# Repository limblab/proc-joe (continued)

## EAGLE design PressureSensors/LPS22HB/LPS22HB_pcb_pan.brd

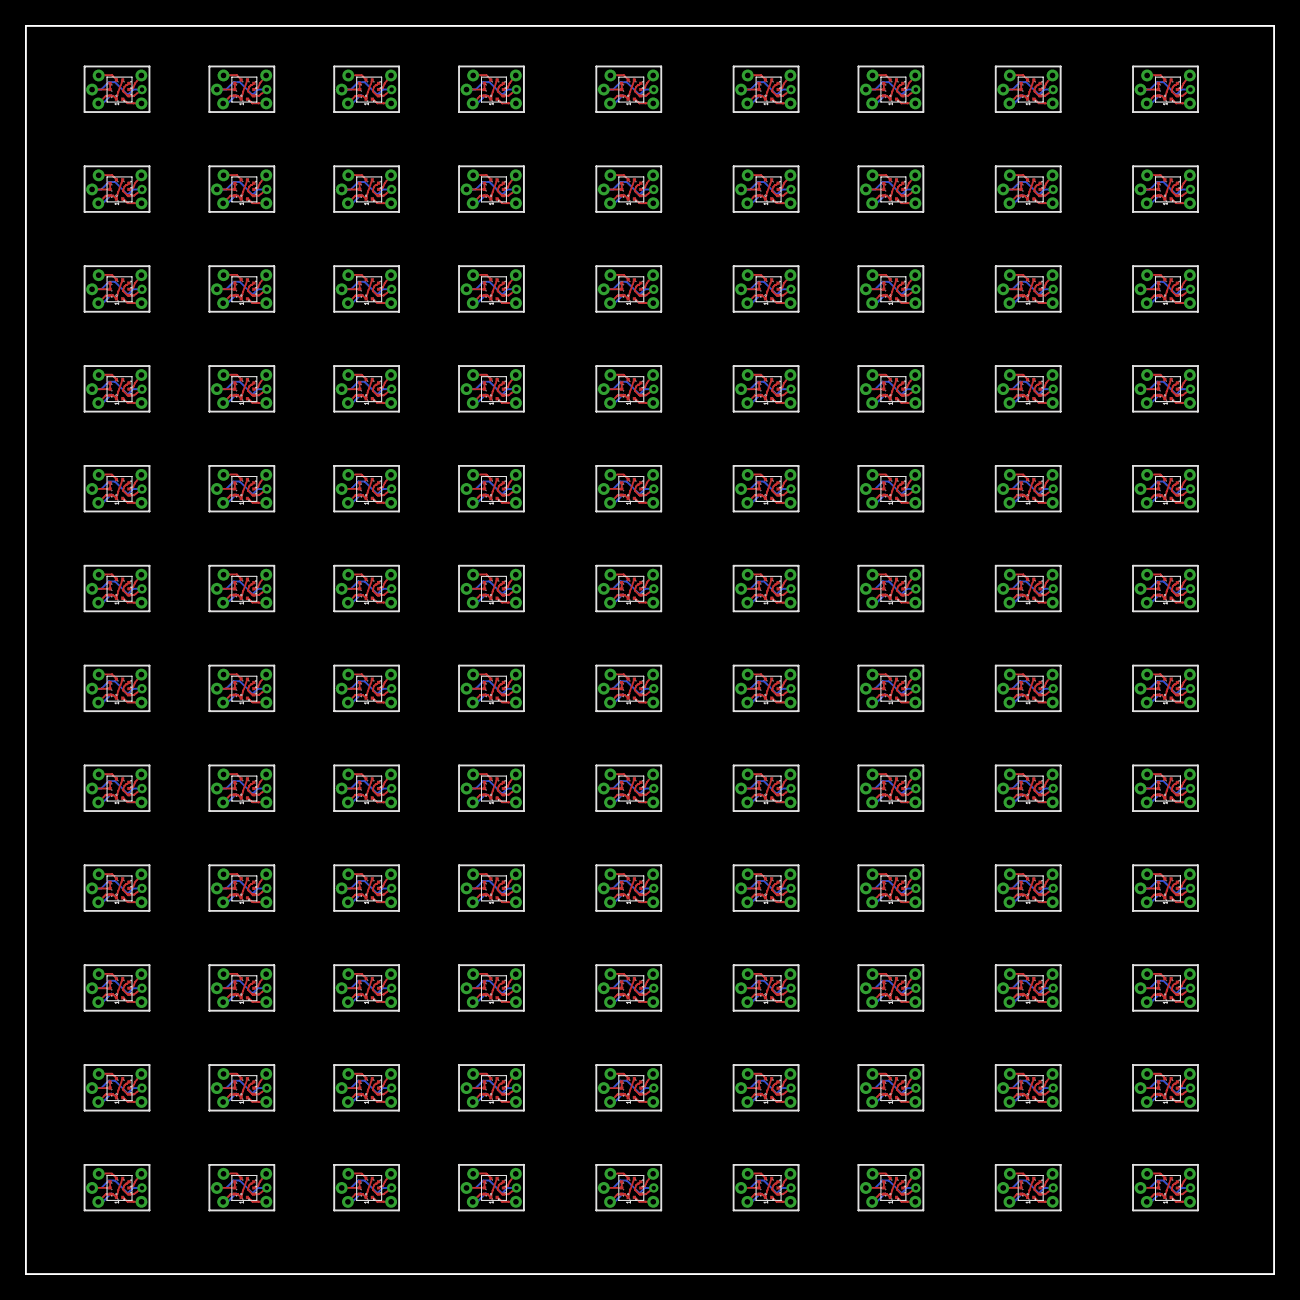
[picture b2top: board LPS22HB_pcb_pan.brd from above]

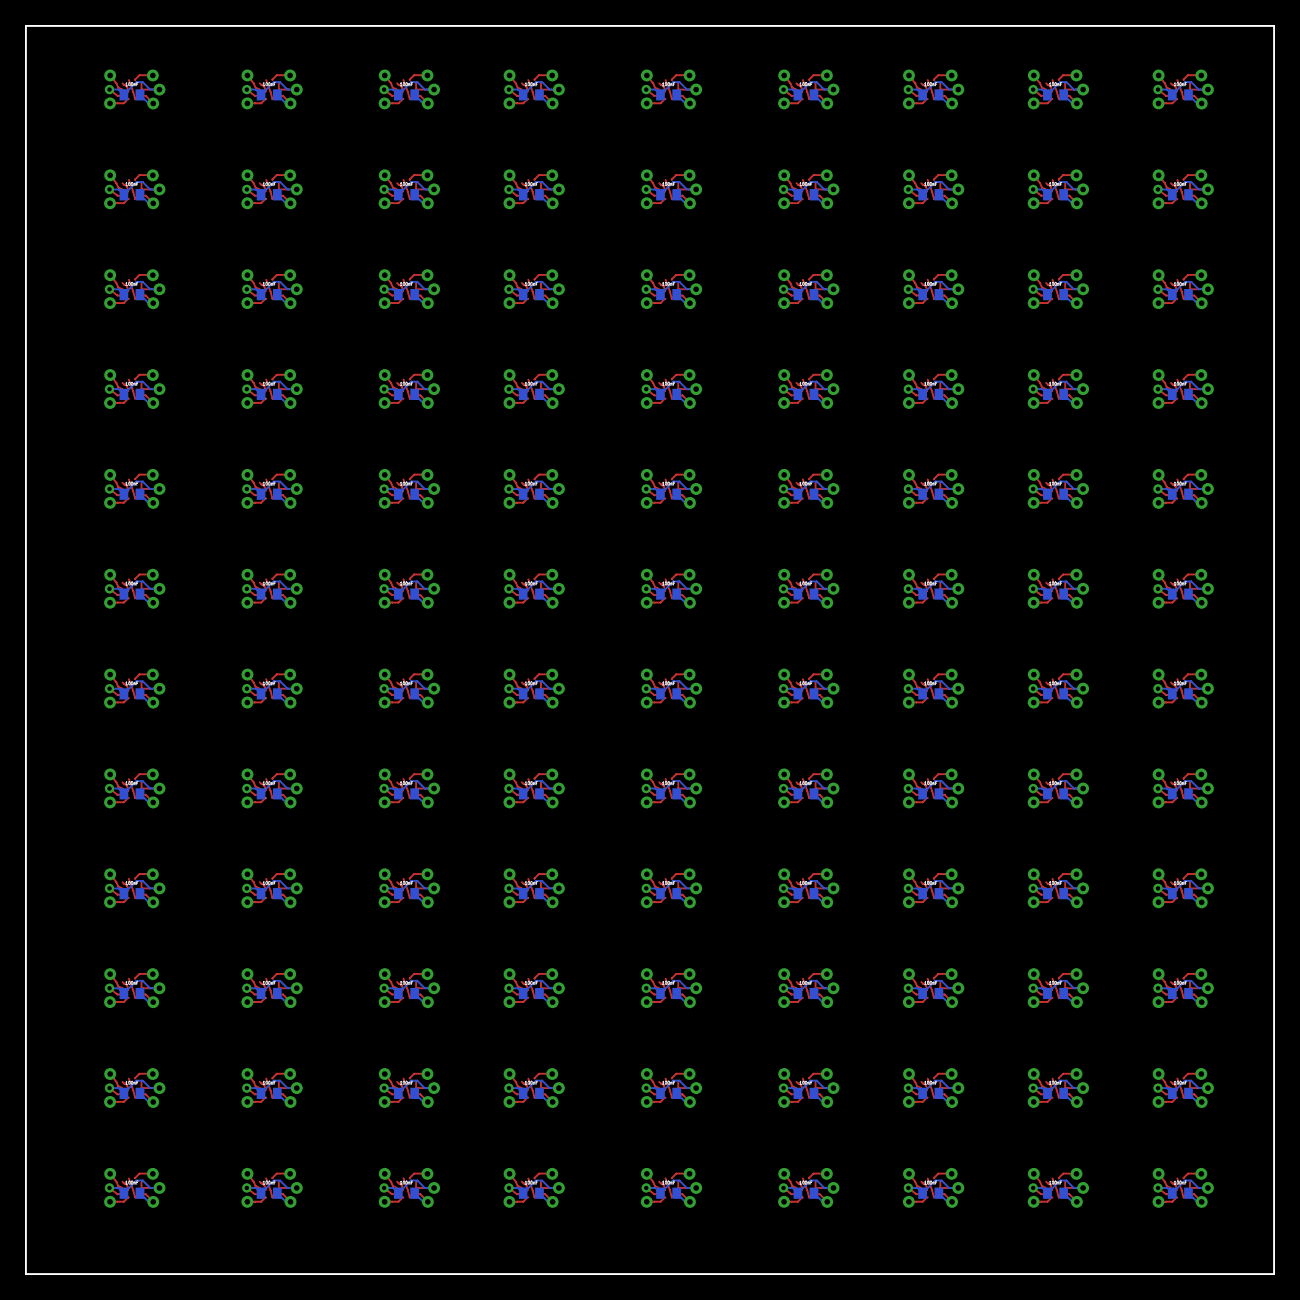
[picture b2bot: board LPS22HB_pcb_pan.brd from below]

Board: 2 copper layers, 100.0 x 100.0 mm, 756 parts (108 on the bottom side), 540 nets.

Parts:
C1, C2, C3, C4, C5, C6, C7, C8, C9, C10, C11, C12, C13, C14, C15, C16, C17, C18, C19, C20, C21, C22, C23, C24, C25, C26, C27, C28, C29, C30, C31, C32, C33, C34, C35, C36, C37, C38, C39, C40, C41, C42, C43, C44, C45, C46, C47, C48, C49, C50, C51, C52, C53, C54, C55, C56, C57, C58, C59, C60, C61, C62, C63, C64, C65, C66, C67, C68, C69, C70, C71, C72, C73, C74, C75, C76, C77, C78, C79, C80, C81, C82, C83, C84, C85, C86, C87, C88, C89, C90, C91, C92, C93, C94, C95, C96, C97, C98, C99, C100, C101, C102, C103, C104, C105, C106, C107, C108: 100nF; C0402
U$1, U$12, U$18, U$24, U$30, U$36, U$42, U$48, U$54, U$60, U$66, U$72, U$78, U$84, U$90, U$96, U$102, U$108, U$114, U$120, U$126, U$132, U$138, U$144, U$150, U$156, U$162, U$168, U$174, U$180, U$186, U$192, U$198, U$204, U$210, U$216, U$222, U$228, U$234, U$240, U$246, U$252, U$258, U$264, U$270, U$276, U$282, U$288, U$294, U$300, U$306, U$312, U$318, U$324, U$330, U$336, U$342, U$348, U$354, U$360, U$366, U$372, U$378, U$384, U$390, U$396, U$402, U$408, U$414, U$420, U$426, U$432, U$438, U$444, U$450, U$456, U$462, U$468, U$474, U$480, U$486, U$492, U$498, U$504, U$510, U$516, U$522, U$528, U$534, U$540, U$546, U$552, U$558, U$564, U$570, U$576, U$582, U$588, U$594, U$600, U$606, U$612, U$618, U$624, U$630, U$636, U$642, U$648: LPS22HB_HLGA
U$2, U$3, U$4, U$5, U$6, U$7, U$8, U$9, U$10, U$11, U$13, U$14, U$15, U$16, U$17, U$19, U$20, U$21, U$22, U$23, U$25, U$26, U$27, U$28, U$29, U$31, U$32, U$33, U$34, U$35, U$37, U$38, U$39, U$40, U$41, U$43, U$44, U$45, U$46, U$47, U$49, U$50, U$51, U$52, U$53, U$55, U$56, U$57, U$58, U$59, U$61, U$62, U$63, U$64, U$65, U$67, U$68, U$69, U$70, U$71, U$73, U$74, U$75, U$76, U$77, U$79, U$80, U$81, U$82, U$83, U$85, U$86, U$87, U$88, U$89, U$91, U$92, U$93, U$94, U$95, U$97, U$98, U$99, U$100, U$101, U$103, U$104, U$105, U$106, U$107, U$109, U$110, U$111, U$112, U$113, U$115, U$116, U$117, U$118, U$119, U$121, U$122, U$123, U$124, U$125, U$127, U$128, U$129, U$130, U$131, U$133, U$134, U$135, U$136, U$137, U$139, U$140, U$141, U$142, U$143, U$145, U$146, U$147, U$148, U$149, U$151, U$152, U$153, U$154, U$155, U$157, U$158, U$159, U$160, U$161, U$163, U$164, U$165, U$166, U$167, U$169, U$170, U$171, U$172, U$173, U$175, U$176, U$177, U$178, U$179, U$181, U$182, U$183, U$184, U$185, U$187, U$188, U$189, U$190, U$191, U$193, U$194, U$195, U$196, U$197, U$199, U$200, U$201, U$202, U$203, U$205, U$206, U$207, U$208, U$209, U$211, U$212, U$213, U$214, U$215, U$217, U$218, U$219, U$220, U$221, U$223, U$224, U$225, U$226, U$227, U$229, U$230, U$231, U$232, U$233, U$235, U$236, U$237, U$238, U$239, U$241, U$242, U$243, U$244, U$245, U$247, U$248, U$249, U$250, U$251, U$253, U$254, U$255, U$256, U$257, U$259, U$260, U$261, U$262, U$263, U$265, U$266, U$267, U$268, U$269, U$271, U$272, U$273, U$274, U$275, U$277, U$278, U$279, U$280, U$281, U$283, U$284, U$285, U$286, U$287, U$289, U$290, U$291, U$292, U$293, U$295, U$296, U$297, U$298, U$299, U$301, U$302, U$303, U$304, U$305, U$307, U$308, U$309, U$310, U$311, U$313, U$314, U$315, U$316, U$317, U$319, U$320, U$321, U$322, U$323, U$325, U$326, U$327, U$328, U$329, U$331, U$332, U$333, U$334, U$335, U$337, U$338, U$339, U$340, U$341, U$343, U$344, U$345, U$346, U$347, U$349, U$350, U$351, U$352, U$353, U$355, U$356, U$357, U$358, U$359, U$361, U$362, U$363, U$364, U$365, U$367, U$368, U$369, U$370, U$371, U$373, U$374, U$375, U$376, U$377, U$379, U$380, U$381, U$382, U$383, U$385, U$386, U$387, U$388, U$389, U$391, U$392, U$393, U$394, U$395, U$397, U$398, U$399, U$400, U$401, U$403, U$404, U$405, U$406, U$407, U$409, U$410, U$411, U$412, U$413, U$415, U$416, U$417, U$418, U$419, U$421, U$422, U$423, U$424, U$425, U$427, U$428, U$429, U$430, U$431, U$433, U$434, U$435, U$436, U$437, U$439, U$440, U$441, U$442, U$443, U$445, U$446, U$447, U$448, U$449, U$451, U$452, U$453, U$454, U$455, U$457, U$458, U$459, U$460, U$461, U$463, U$464, U$465, U$466, U$467, U$469, U$470, U$471, U$472, U$473, U$475, U$476, U$477, U$478, U$479, U$481, U$482, U$483, U$484, U$485, U$487, U$488, U$489, U$490, U$491, U$493, U$494, U$495, U$496, U$497, U$499, U$500, U$501, U$502, U$503, U$505, U$506, U$507, U$508, U$509, U$511, U$512, U$513, U$514, U$515, U$517, U$518, U$519, U$520, U$521, U$523, U$524, U$525, U$526, U$527, U$529, U$530, U$531, U$532, U$533, U$535, U$536, U$537, U$538, U$539, U$541, U$542, U$543, U$544, U$545, U$547, U$548, U$549, U$550, U$551, U$553, U$554, U$555, U$556, U$557, U$559, U$560, U$561, U$562, U$563, U$565, U$566, U$567, U$568, U$569, U$571, U$572, U$573, U$574, U$575, U$577, U$578, U$579, U$580, U$581, U$583, U$584, U$585, U$586, U$587, U$589, U$590, U$591, U$592, U$593, U$595, U$596, U$597, U$598, U$599, U$601, U$602, U$603, U$604, U$605, U$607, U$608, U$609, U$610, U$611, U$613, U$614, U$615, U$616, U$617, U$619, U$620, U$621, U$622, U$623, U$625, U$626, U$627, U$628, U$629, U$631, U$632, U$633, U$634, U$635, U$637, U$638, U$639, U$640, U$641, U$643, U$644, U$645, U$646, U$647: WIREPAD_0,8/0,45

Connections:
+3V1: C1.1, U$11.P$1, U$12.P$1, U$12.P$6, U$12.P$10
+3V2: C3.1, U$17.P$1, U$18.P$1, U$18.P$6, U$18.P$10
+3V3: C2.1, U$1.P$1, U$1.P$6, U$1.P$10, U$8.P$1
+3V4: C4.1, U$23.P$1, U$24.P$1, U$24.P$6, U$24.P$10
+3V5: C5.1, U$29.P$1, U$30.P$1, U$30.P$6, U$30.P$10
+3V6: C6.1, U$35.P$1, U$36.P$1, U$36.P$6, U$36.P$10
+3V7: C7.1, U$41.P$1, U$42.P$1, U$42.P$6, U$42.P$10
+3V8: C8.1, U$47.P$1, U$48.P$1, U$48.P$6, U$48.P$10
+3V9: C9.1, U$53.P$1, U$54.P$1, U$54.P$6, U$54.P$10
+3V10: C10.1, U$59.P$1, U$60.P$1, U$60.P$6, U$60.P$10
+3V11: C11.1, U$65.P$1, U$66.P$1, U$66.P$6, U$66.P$10
+3V12: C12.1, U$71.P$1, U$72.P$1, U$72.P$6, U$72.P$10
+3V13: C13.1, U$77.P$1, U$78.P$1, U$78.P$6, U$78.P$10
+3V14: C14.1, U$83.P$1, U$84.P$1, U$84.P$6, U$84.P$10
+3V15: C15.1, U$89.P$1, U$90.P$1, U$90.P$6, U$90.P$10
+3V16: C16.1, U$95.P$1, U$96.P$1, U$96.P$6, U$96.P$10
+3V17: C17.1, U$101.P$1, U$102.P$1, U$102.P$6, U$102.P$10
+3V18: C18.1, U$107.P$1, U$108.P$1, U$108.P$6, U$108.P$10
+3V19: C19.1, U$113.P$1, U$114.P$1, U$114.P$6, U$114.P$10
+3V20: C20.1, U$119.P$1, U$120.P$1, U$120.P$6, U$120.P$10
+3V21: C21.1, U$125.P$1, U$126.P$1, U$126.P$6, U$126.P$10
+3V22: C22.1, U$131.P$1, U$132.P$1, U$132.P$6, U$132.P$10
+3V23: C23.1, U$137.P$1, U$138.P$1, U$138.P$6, U$138.P$10
+3V24: C24.1, U$143.P$1, U$144.P$1, U$144.P$6, U$144.P$10
+3V25: C25.1, U$149.P$1, U$150.P$1, U$150.P$6, U$150.P$10
+3V26: C26.1, U$155.P$1, U$156.P$1, U$156.P$6, U$156.P$10
+3V27: C27.1, U$161.P$1, U$162.P$1, U$162.P$6, U$162.P$10
+3V28: C28.1, U$167.P$1, U$168.P$1, U$168.P$6, U$168.P$10
+3V29: C29.1, U$173.P$1, U$174.P$1, U$174.P$6, U$174.P$10
+3V30: C30.1, U$179.P$1, U$180.P$1, U$180.P$6, U$180.P$10
+3V31: C31.1, U$185.P$1, U$186.P$1, U$186.P$6, U$186.P$10
+3V32: C32.1, U$191.P$1, U$192.P$1, U$192.P$6, U$192.P$10
+3V33: C33.1, U$197.P$1, U$198.P$1, U$198.P$6, U$198.P$10
+3V34: C34.1, U$203.P$1, U$204.P$1, U$204.P$6, U$204.P$10
+3V35: C35.1, U$209.P$1, U$210.P$1, U$210.P$6, U$210.P$10
+3V36: C36.1, U$215.P$1, U$216.P$1, U$216.P$6, U$216.P$10
+3V37: C37.1, U$221.P$1, U$222.P$1, U$222.P$6, U$222.P$10
+3V38: C38.1, U$227.P$1, U$228.P$1, U$228.P$6, U$228.P$10
+3V39: C39.1, U$233.P$1, U$234.P$1, U$234.P$6, U$234.P$10
+3V40: C40.1, U$239.P$1, U$240.P$1, U$240.P$6, U$240.P$10
+3V41: C41.1, U$245.P$1, U$246.P$1, U$246.P$6, U$246.P$10
+3V42: C42.1, U$251.P$1, U$252.P$1, U$252.P$6, U$252.P$10
+3V43: C43.1, U$257.P$1, U$258.P$1, U$258.P$6, U$258.P$10
+3V44: C44.1, U$263.P$1, U$264.P$1, U$264.P$6, U$264.P$10
+3V45: C45.1, U$269.P$1, U$270.P$1, U$270.P$6, U$270.P$10
+3V46: C46.1, U$275.P$1, U$276.P$1, U$276.P$6, U$276.P$10
+3V47: C47.1, U$281.P$1, U$282.P$1, U$282.P$6, U$282.P$10
+3V48: C48.1, U$287.P$1, U$288.P$1, U$288.P$6, U$288.P$10
+3V49: C49.1, U$293.P$1, U$294.P$1, U$294.P$6, U$294.P$10
+3V50: C50.1, U$299.P$1, U$300.P$1, U$300.P$6, U$300.P$10
+3V51: C51.1, U$305.P$1, U$306.P$1, U$306.P$6, U$306.P$10
+3V52: C52.1, U$311.P$1, U$312.P$1, U$312.P$6, U$312.P$10
+3V53: C53.1, U$317.P$1, U$318.P$1, U$318.P$6, U$318.P$10
+3V54: C54.1, U$323.P$1, U$324.P$1, U$324.P$6, U$324.P$10
+3V55: C55.1, U$329.P$1, U$330.P$1, U$330.P$6, U$330.P$10
+3V56: C56.1, U$335.P$1, U$336.P$1, U$336.P$6, U$336.P$10
+3V57: C57.1, U$341.P$1, U$342.P$1, U$342.P$6, U$342.P$10
+3V58: C58.1, U$347.P$1, U$348.P$1, U$348.P$6, U$348.P$10
+3V59: C59.1, U$353.P$1, U$354.P$1, U$354.P$6, U$354.P$10
+3V60: C60.1, U$359.P$1, U$360.P$1, U$360.P$6, U$360.P$10
+3V61: C61.1, U$365.P$1, U$366.P$1, U$366.P$6, U$366.P$10
+3V62: C62.1, U$371.P$1, U$372.P$1, U$372.P$6, U$372.P$10
+3V63: C63.1, U$377.P$1, U$378.P$1, U$378.P$6, U$378.P$10
+3V64: C64.1, U$383.P$1, U$384.P$1, U$384.P$6, U$384.P$10
+3V65: C65.1, U$389.P$1, U$390.P$1, U$390.P$6, U$390.P$10
+3V66: C66.1, U$395.P$1, U$396.P$1, U$396.P$6, U$396.P$10
+3V67: C67.1, U$401.P$1, U$402.P$1, U$402.P$6, U$402.P$10
+3V68: C68.1, U$407.P$1, U$408.P$1, U$408.P$6, U$408.P$10
+3V69: C69.1, U$413.P$1, U$414.P$1, U$414.P$6, U$414.P$10
+3V70: C70.1, U$419.P$1, U$420.P$1, U$420.P$6, U$420.P$10
+3V71: C71.1, U$425.P$1, U$426.P$1, U$426.P$6, U$426.P$10
+3V72: C72.1, U$431.P$1, U$432.P$1, U$432.P$6, U$432.P$10
+3V73: C73.1, U$437.P$1, U$438.P$1, U$438.P$6, U$438.P$10
+3V74: C74.1, U$443.P$1, U$444.P$1, U$444.P$6, U$444.P$10
+3V75: C75.1, U$449.P$1, U$450.P$1, U$450.P$6, U$450.P$10
+3V76: C76.1, U$455.P$1, U$456.P$1, U$456.P$6, U$456.P$10
+3V77: C77.1, U$461.P$1, U$462.P$1, U$462.P$6, U$462.P$10
+3V78: C78.1, U$467.P$1, U$468.P$1, U$468.P$6, U$468.P$10
+3V79: C79.1, U$473.P$1, U$474.P$1, U$474.P$6, U$474.P$10
+3V80: C80.1, U$479.P$1, U$480.P$1, U$480.P$6, U$480.P$10
+3V81: C81.1, U$485.P$1, U$486.P$1, U$486.P$6, U$486.P$10
+3V82: C82.1, U$491.P$1, U$492.P$1, U$492.P$6, U$492.P$10
+3V83: C83.1, U$497.P$1, U$498.P$1, U$498.P$6, U$498.P$10
+3V84: C84.1, U$503.P$1, U$504.P$1, U$504.P$6, U$504.P$10
+3V85: C85.1, U$509.P$1, U$510.P$1, U$510.P$6, U$510.P$10
+3V86: C86.1, U$515.P$1, U$516.P$1, U$516.P$6, U$516.P$10
+3V87: C87.1, U$521.P$1, U$522.P$1, U$522.P$6, U$522.P$10
+3V88: C88.1, U$527.P$1, U$528.P$1, U$528.P$6, U$528.P$10
+3V89: C89.1, U$533.P$1, U$534.P$1, U$534.P$6, U$534.P$10
+3V90: C90.1, U$539.P$1, U$540.P$1, U$540.P$6, U$540.P$10
+3V91: C91.1, U$545.P$1, U$546.P$1, U$546.P$6, U$546.P$10
+3V92: C92.1, U$551.P$1, U$552.P$1, U$552.P$6, U$552.P$10
+3V93: C93.1, U$557.P$1, U$558.P$1, U$558.P$6, U$558.P$10
+3V94: C94.1, U$563.P$1, U$564.P$1, U$564.P$6, U$564.P$10
+3V95: C95.1, U$569.P$1, U$570.P$1, U$570.P$6, U$570.P$10
+3V96: C96.1, U$575.P$1, U$576.P$1, U$576.P$6, U$576.P$10
+3V97: C97.1, U$581.P$1, U$582.P$1, U$582.P$6, U$582.P$10
+3V98: C98.1, U$587.P$1, U$588.P$1, U$588.P$6, U$588.P$10
+3V99: C99.1, U$593.P$1, U$594.P$1, U$594.P$6, U$594.P$10
+3V100: C100.1, U$599.P$1, U$600.P$1, U$600.P$6, U$600.P$10
+3V101: C101.1, U$605.P$1, U$606.P$1, U$606.P$6, U$606.P$10
+3V102: C102.1, U$611.P$1, U$612.P$1, U$612.P$6, U$612.P$10
+3V103: C103.1, U$617.P$1, U$618.P$1, U$618.P$6, U$618.P$10
+3V104: C104.1, U$623.P$1, U$624.P$1, U$624.P$6, U$624.P$10
+3V105: C105.1, U$629.P$1, U$630.P$1, U$630.P$6, U$630.P$10
+3V106: C106.1, U$635.P$1, U$636.P$1, U$636.P$6, U$636.P$10
+3V107: C107.1, U$641.P$1, U$642.P$1, U$642.P$6, U$642.P$10
+3V108: C108.1, U$647.P$1, U$648.P$1, U$648.P$6, U$648.P$10
GND: C2.2, U$1.P$3, U$1.P$5, U$1.P$8, U$1.P$9, U$7.P$1
GND1: C1.2, U$10.P$1, U$12.P$3, U$12.P$5, U$12.P$8, U$12.P$9
GND2: C3.2, U$16.P$1, U$18.P$3, U$18.P$5, U$18.P$8, U$18.P$9
GND3: C4.2, U$22.P$1, U$24.P$3, U$24.P$5, U$24.P$8, U$24.P$9
GND4: C5.2, U$28.P$1, U$30.P$3, U$30.P$5, U$30.P$8, U$30.P$9
GND5: C6.2, U$34.P$1, U$36.P$3, U$36.P$5, U$36.P$8, U$36.P$9
GND6: C7.2, U$40.P$1, U$42.P$3, U$42.P$5, U$42.P$8, U$42.P$9
GND7: C8.2, U$46.P$1, U$48.P$3, U$48.P$5, U$48.P$8, U$48.P$9
GND8: C9.2, U$52.P$1, U$54.P$3, U$54.P$5, U$54.P$8, U$54.P$9
GND9: C10.2, U$58.P$1, U$60.P$3, U$60.P$5, U$60.P$8, U$60.P$9
GND10: C11.2, U$64.P$1, U$66.P$3, U$66.P$5, U$66.P$8, U$66.P$9
GND11: C12.2, U$70.P$1, U$72.P$3, U$72.P$5, U$72.P$8, U$72.P$9
GND12: C13.2, U$76.P$1, U$78.P$3, U$78.P$5, U$78.P$8, U$78.P$9
GND13: C14.2, U$82.P$1, U$84.P$3, U$84.P$5, U$84.P$8, U$84.P$9
GND14: C15.2, U$88.P$1, U$90.P$3, U$90.P$5, U$90.P$8, U$90.P$9
GND15: C16.2, U$94.P$1, U$96.P$3, U$96.P$5, U$96.P$8, U$96.P$9
GND16: C17.2, U$100.P$1, U$102.P$3, U$102.P$5, U$102.P$8, U$102.P$9
GND17: C18.2, U$106.P$1, U$108.P$3, U$108.P$5, U$108.P$8, U$108.P$9
GND18: C19.2, U$112.P$1, U$114.P$3, U$114.P$5, U$114.P$8, U$114.P$9
GND19: C20.2, U$118.P$1, U$120.P$3, U$120.P$5, U$120.P$8, U$120.P$9
GND20: C21.2, U$124.P$1, U$126.P$3, U$126.P$5, U$126.P$8, U$126.P$9
GND21: C22.2, U$130.P$1, U$132.P$3, U$132.P$5, U$132.P$8, U$132.P$9
GND22: C23.2, U$136.P$1, U$138.P$3, U$138.P$5, U$138.P$8, U$138.P$9
GND23: C24.2, U$142.P$1, U$144.P$3, U$144.P$5, U$144.P$8, U$144.P$9
GND24: C25.2, U$148.P$1, U$150.P$3, U$150.P$5, U$150.P$8, U$150.P$9
GND25: C26.2, U$154.P$1, U$156.P$3, U$156.P$5, U$156.P$8, U$156.P$9
GND26: C27.2, U$160.P$1, U$162.P$3, U$162.P$5, U$162.P$8, U$162.P$9
GND27: C28.2, U$166.P$1, U$168.P$3, U$168.P$5, U$168.P$8, U$168.P$9
GND28: C29.2, U$172.P$1, U$174.P$3, U$174.P$5, U$174.P$8, U$174.P$9
GND29: C30.2, U$178.P$1, U$180.P$3, U$180.P$5, U$180.P$8, U$180.P$9
GND30: C31.2, U$184.P$1, U$186.P$3, U$186.P$5, U$186.P$8, U$186.P$9
GND31: C32.2, U$190.P$1, U$192.P$3, U$192.P$5, U$192.P$8, U$192.P$9
GND32: C33.2, U$196.P$1, U$198.P$3, U$198.P$5, U$198.P$8, U$198.P$9
GND33: C34.2, U$202.P$1, U$204.P$3, U$204.P$5, U$204.P$8, U$204.P$9
GND34: C35.2, U$208.P$1, U$210.P$3, U$210.P$5, U$210.P$8, U$210.P$9
GND35: C36.2, U$214.P$1, U$216.P$3, U$216.P$5, U$216.P$8, U$216.P$9
GND36: C37.2, U$220.P$1, U$222.P$3, U$222.P$5, U$222.P$8, U$222.P$9
GND37: C38.2, U$226.P$1, U$228.P$3, U$228.P$5, U$228.P$8, U$228.P$9
GND38: C39.2, U$232.P$1, U$234.P$3, U$234.P$5, U$234.P$8, U$234.P$9
GND39: C40.2, U$238.P$1, U$240.P$3, U$240.P$5, U$240.P$8, U$240.P$9
GND40: C41.2, U$244.P$1, U$246.P$3, U$246.P$5, U$246.P$8, U$246.P$9
GND41: C42.2, U$250.P$1, U$252.P$3, U$252.P$5, U$252.P$8, U$252.P$9
GND42: C43.2, U$256.P$1, U$258.P$3, U$258.P$5, U$258.P$8, U$258.P$9
GND43: C44.2, U$262.P$1, U$264.P$3, U$264.P$5, U$264.P$8, U$264.P$9
GND44: C45.2, U$268.P$1, U$270.P$3, U$270.P$5, U$270.P$8, U$270.P$9
GND45: C46.2, U$274.P$1, U$276.P$3, U$276.P$5, U$276.P$8, U$276.P$9
GND46: C47.2, U$280.P$1, U$282.P$3, U$282.P$5, U$282.P$8, U$282.P$9
GND47: C48.2, U$286.P$1, U$288.P$3, U$288.P$5, U$288.P$8, U$288.P$9
GND48: C49.2, U$292.P$1, U$294.P$3, U$294.P$5, U$294.P$8, U$294.P$9
GND49: C50.2, U$298.P$1, U$300.P$3, U$300.P$5, U$300.P$8, U$300.P$9
GND50: C51.2, U$304.P$1, U$306.P$3, U$306.P$5, U$306.P$8, U$306.P$9
GND51: C52.2, U$310.P$1, U$312.P$3, U$312.P$5, U$312.P$8, U$312.P$9
GND52: C53.2, U$316.P$1, U$318.P$3, U$318.P$5, U$318.P$8, U$318.P$9
GND53: C54.2, U$322.P$1, U$324.P$3, U$324.P$5, U$324.P$8, U$324.P$9
GND54: C55.2, U$328.P$1, U$330.P$3, U$330.P$5, U$330.P$8, U$330.P$9
GND55: C56.2, U$334.P$1, U$336.P$3, U$336.P$5, U$336.P$8, U$336.P$9
GND56: C57.2, U$340.P$1, U$342.P$3, U$342.P$5, U$342.P$8, U$342.P$9
GND57: C58.2, U$346.P$1, U$348.P$3, U$348.P$5, U$348.P$8, U$348.P$9
GND58: C59.2, U$352.P$1, U$354.P$3, U$354.P$5, U$354.P$8, U$354.P$9
GND59: C60.2, U$358.P$1, U$360.P$3, U$360.P$5, U$360.P$8, U$360.P$9
GND60: C61.2, U$364.P$1, U$366.P$3, U$366.P$5, U$366.P$8, U$366.P$9
GND61: C62.2, U$370.P$1, U$372.P$3, U$372.P$5, U$372.P$8, U$372.P$9
GND62: C63.2, U$376.P$1, U$378.P$3, U$378.P$5, U$378.P$8, U$378.P$9
GND63: C64.2, U$382.P$1, U$384.P$3, U$384.P$5, U$384.P$8, U$384.P$9
GND64: C65.2, U$388.P$1, U$390.P$3, U$390.P$5, U$390.P$8, U$390.P$9
GND65: C66.2, U$394.P$1, U$396.P$3, U$396.P$5, U$396.P$8, U$396.P$9
GND66: C67.2, U$400.P$1, U$402.P$3, U$402.P$5, U$402.P$8, U$402.P$9
GND67: C68.2, U$406.P$1, U$408.P$3, U$408.P$5, U$408.P$8, U$408.P$9
GND68: C69.2, U$412.P$1, U$414.P$3, U$414.P$5, U$414.P$8, U$414.P$9
GND69: C70.2, U$418.P$1, U$420.P$3, U$420.P$5, U$420.P$8, U$420.P$9
GND70: C71.2, U$424.P$1, U$426.P$3, U$426.P$5, U$426.P$8, U$426.P$9
GND71: C72.2, U$430.P$1, U$432.P$3, U$432.P$5, U$432.P$8, U$432.P$9
GND72: C73.2, U$436.P$1, U$438.P$3, U$438.P$5, U$438.P$8, U$438.P$9
GND73: C74.2, U$442.P$1, U$444.P$3, U$444.P$5, U$444.P$8, U$444.P$9
GND74: C75.2, U$448.P$1, U$450.P$3, U$450.P$5, U$450.P$8, U$450.P$9
GND75: C76.2, U$454.P$1, U$456.P$3, U$456.P$5, U$456.P$8, U$456.P$9
GND76: C77.2, U$460.P$1, U$462.P$3, U$462.P$5, U$462.P$8, U$462.P$9
GND77: C78.2, U$466.P$1, U$468.P$3, U$468.P$5, U$468.P$8, U$468.P$9
GND78: C79.2, U$472.P$1, U$474.P$3, U$474.P$5, U$474.P$8, U$474.P$9
GND79: C80.2, U$478.P$1, U$480.P$3, U$480.P$5, U$480.P$8, U$480.P$9
GND80: C81.2, U$484.P$1, U$486.P$3, U$486.P$5, U$486.P$8, U$486.P$9
GND81: C82.2, U$490.P$1, U$492.P$3, U$492.P$5, U$492.P$8, U$492.P$9
GND82: C83.2, U$496.P$1, U$498.P$3, U$498.P$5, U$498.P$8, U$498.P$9
GND83: C84.2, U$502.P$1, U$504.P$3, U$504.P$5, U$504.P$8, U$504.P$9
GND84: C85.2, U$508.P$1, U$510.P$3, U$510.P$5, U$510.P$8, U$510.P$9
GND85: C86.2, U$514.P$1, U$516.P$3, U$516.P$5, U$516.P$8, U$516.P$9
GND86: C87.2, U$520.P$1, U$522.P$3, U$522.P$5, U$522.P$8, U$522.P$9
GND87: C88.2, U$526.P$1, U$528.P$3, U$528.P$5, U$528.P$8, U$528.P$9
GND88: C89.2, U$532.P$1, U$534.P$3, U$534.P$5, U$534.P$8, U$534.P$9
GND89: C90.2, U$538.P$1, U$540.P$3, U$540.P$5, U$540.P$8, U$540.P$9
GND90: C91.2, U$544.P$1, U$546.P$3, U$546.P$5, U$546.P$8, U$546.P$9
GND91: C92.2, U$550.P$1, U$552.P$3, U$552.P$5, U$552.P$8, U$552.P$9
GND92: C93.2, U$556.P$1, U$558.P$3, U$558.P$5, U$558.P$8, U$558.P$9
GND93: C94.2, U$562.P$1, U$564.P$3, U$564.P$5, U$564.P$8, U$564.P$9
GND94: C95.2, U$568.P$1, U$570.P$3, U$570.P$5, U$570.P$8, U$570.P$9
GND95: C96.2, U$574.P$1, U$576.P$3, U$576.P$5, U$576.P$8, U$576.P$9
GND96: C97.2, U$580.P$1, U$582.P$3, U$582.P$5, U$582.P$8, U$582.P$9
GND97: C98.2, U$586.P$1, U$588.P$3, U$588.P$5, U$588.P$8, U$588.P$9
GND98: C99.2, U$592.P$1, U$594.P$3, U$594.P$5, U$594.P$8, U$594.P$9
GND99: C100.2, U$598.P$1, U$600.P$3, U$600.P$5, U$600.P$8, U$600.P$9
GND100: C101.2, U$604.P$1, U$606.P$3, U$606.P$5, U$606.P$8, U$606.P$9
GND101: C102.2, U$610.P$1, U$612.P$3, U$612.P$5, U$612.P$8, U$612.P$9
GND102: C103.2, U$616.P$1, U$618.P$3, U$618.P$5, U$618.P$8, U$618.P$9
GND103: C104.2, U$622.P$1, U$624.P$3, U$624.P$5, U$624.P$8, U$624.P$9
GND104: C105.2, U$628.P$1, U$630.P$3, U$630.P$5, U$630.P$8, U$630.P$9
GND105: C106.2, U$634.P$1, U$636.P$3, U$636.P$5, U$636.P$8, U$636.P$9
GND106: C107.2, U$640.P$1, U$642.P$3, U$642.P$5, U$642.P$8, U$642.P$9
GND107: C108.2, U$646.P$1, U$648.P$3, U$648.P$5, U$648.P$8, U$648.P$9
unnamed: U$5.P$1, U$12.P$4
unnamed: U$4.P$1, U$12.P$2
unnamed: U$9.P$1, U$12.P$7
unnamed: U$1.P$4, U$3.P$1
unnamed: U$1.P$2, U$2.P$1
unnamed: U$1.P$7, U$6.P$1
unnamed: U$14.P$1, U$18.P$4
unnamed: U$13.P$1, U$18.P$2
unnamed: U$15.P$1, U$18.P$7
unnamed: U$20.P$1, U$24.P$4
unnamed: U$19.P$1, U$24.P$2
unnamed: U$21.P$1, U$24.P$7
unnamed: U$26.P$1, U$30.P$4
unnamed: U$25.P$1, U$30.P$2
unnamed: U$27.P$1, U$30.P$7
unnamed: U$32.P$1, U$36.P$4
unnamed: U$31.P$1, U$36.P$2
unnamed: U$33.P$1, U$36.P$7
unnamed: U$38.P$1, U$42.P$4
unnamed: U$37.P$1, U$42.P$2
unnamed: U$39.P$1, U$42.P$7
unnamed: U$44.P$1, U$48.P$4
unnamed: U$43.P$1, U$48.P$2
unnamed: U$45.P$1, U$48.P$7
unnamed: U$50.P$1, U$54.P$4
unnamed: U$49.P$1, U$54.P$2
unnamed: U$51.P$1, U$54.P$7
unnamed: U$56.P$1, U$60.P$4
unnamed: U$55.P$1, U$60.P$2
unnamed: U$57.P$1, U$60.P$7
unnamed: U$62.P$1, U$66.P$4
unnamed: U$61.P$1, U$66.P$2
unnamed: U$63.P$1, U$66.P$7
unnamed: U$68.P$1, U$72.P$4
unnamed: U$67.P$1, U$72.P$2
unnamed: U$69.P$1, U$72.P$7
unnamed: U$74.P$1, U$78.P$4
unnamed: U$73.P$1, U$78.P$2
unnamed: U$75.P$1, U$78.P$7
unnamed: U$80.P$1, U$84.P$4
unnamed: U$79.P$1, U$84.P$2
unnamed: U$81.P$1, U$84.P$7
unnamed: U$86.P$1, U$90.P$4
unnamed: U$85.P$1, U$90.P$2
unnamed: U$87.P$1, U$90.P$7
unnamed: U$92.P$1, U$96.P$4
unnamed: U$91.P$1, U$96.P$2
unnamed: U$93.P$1, U$96.P$7
unnamed: U$98.P$1, U$102.P$4
unnamed: U$97.P$1, U$102.P$2
unnamed: U$99.P$1, U$102.P$7
unnamed: U$104.P$1, U$108.P$4
unnamed: U$103.P$1, U$108.P$2
unnamed: U$105.P$1, U$108.P$7
unnamed: U$110.P$1, U$114.P$4
unnamed: U$109.P$1, U$114.P$2
unnamed: U$111.P$1, U$114.P$7
unnamed: U$116.P$1, U$120.P$4
unnamed: U$115.P$1, U$120.P$2
unnamed: U$117.P$1, U$120.P$7
unnamed: U$122.P$1, U$126.P$4
unnamed: U$121.P$1, U$126.P$2
unnamed: U$123.P$1, U$126.P$7
unnamed: U$128.P$1, U$132.P$4
unnamed: U$127.P$1, U$132.P$2
unnamed: U$129.P$1, U$132.P$7
unnamed: U$134.P$1, U$138.P$4
unnamed: U$133.P$1, U$138.P$2
unnamed: U$135.P$1, U$138.P$7
unnamed: U$140.P$1, U$144.P$4
unnamed: U$139.P$1, U$144.P$2
unnamed: U$141.P$1, U$144.P$7
unnamed: U$146.P$1, U$150.P$4
unnamed: U$145.P$1, U$150.P$2
unnamed: U$147.P$1, U$150.P$7
unnamed: U$152.P$1, U$156.P$4
unnamed: U$151.P$1, U$156.P$2
unnamed: U$153.P$1, U$156.P$7
unnamed: U$158.P$1, U$162.P$4
unnamed: U$157.P$1, U$162.P$2
unnamed: U$159.P$1, U$162.P$7
unnamed: U$164.P$1, U$168.P$4
unnamed: U$163.P$1, U$168.P$2
unnamed: U$165.P$1, U$168.P$7
unnamed: U$170.P$1, U$174.P$4
unnamed: U$169.P$1, U$174.P$2
unnamed: U$171.P$1, U$174.P$7
unnamed: U$176.P$1, U$180.P$4
unnamed: U$175.P$1, U$180.P$2
unnamed: U$177.P$1, U$180.P$7
unnamed: U$182.P$1, U$186.P$4
unnamed: U$181.P$1, U$186.P$2
unnamed: U$183.P$1, U$186.P$7
unnamed: U$188.P$1, U$192.P$4
unnamed: U$187.P$1, U$192.P$2
unnamed: U$189.P$1, U$192.P$7
unnamed: U$194.P$1, U$198.P$4
unnamed: U$193.P$1, U$198.P$2
unnamed: U$195.P$1, U$198.P$7
unnamed: U$200.P$1, U$204.P$4
unnamed: U$199.P$1, U$204.P$2
unnamed: U$201.P$1, U$204.P$7
unnamed: U$206.P$1, U$210.P$4
unnamed: U$205.P$1, U$210.P$2
unnamed: U$207.P$1, U$210.P$7
unnamed: U$212.P$1, U$216.P$4
unnamed: U$211.P$1, U$216.P$2
unnamed: U$213.P$1, U$216.P$7
unnamed: U$218.P$1, U$222.P$4
unnamed: U$217.P$1, U$222.P$2
unnamed: U$219.P$1, U$222.P$7
unnamed: U$224.P$1, U$228.P$4
unnamed: U$223.P$1, U$228.P$2
unnamed: U$225.P$1, U$228.P$7
unnamed: U$230.P$1, U$234.P$4
unnamed: U$229.P$1, U$234.P$2
unnamed: U$231.P$1, U$234.P$7
unnamed: U$236.P$1, U$240.P$4
unnamed: U$235.P$1, U$240.P$2
unnamed: U$237.P$1, U$240.P$7
unnamed: U$242.P$1, U$246.P$4
unnamed: U$241.P$1, U$246.P$2
unnamed: U$243.P$1, U$246.P$7
unnamed: U$248.P$1, U$252.P$4
unnamed: U$247.P$1, U$252.P$2
unnamed: U$249.P$1, U$252.P$7
unnamed: U$254.P$1, U$258.P$4
unnamed: U$253.P$1, U$258.P$2
unnamed: U$255.P$1, U$258.P$7
unnamed: U$260.P$1, U$264.P$4
unnamed: U$259.P$1, U$264.P$2
unnamed: U$261.P$1, U$264.P$7
unnamed: U$266.P$1, U$270.P$4
unnamed: U$265.P$1, U$270.P$2
unnamed: U$267.P$1, U$270.P$7
unnamed: U$272.P$1, U$276.P$4
unnamed: U$271.P$1, U$276.P$2
unnamed: U$273.P$1, U$276.P$7
unnamed: U$278.P$1, U$282.P$4
unnamed: U$277.P$1, U$282.P$2
unnamed: U$279.P$1, U$282.P$7
unnamed: U$284.P$1, U$288.P$4
unnamed: U$283.P$1, U$288.P$2
unnamed: U$285.P$1, U$288.P$7
unnamed: U$290.P$1, U$294.P$4
unnamed: U$289.P$1, U$294.P$2
unnamed: U$291.P$1, U$294.P$7
unnamed: U$296.P$1, U$300.P$4
unnamed: U$295.P$1, U$300.P$2
unnamed: U$297.P$1, U$300.P$7
unnamed: U$302.P$1, U$306.P$4
unnamed: U$301.P$1, U$306.P$2
unnamed: U$303.P$1, U$306.P$7
unnamed: U$308.P$1, U$312.P$4
unnamed: U$307.P$1, U$312.P$2
unnamed: U$309.P$1, U$312.P$7
unnamed: U$314.P$1, U$318.P$4
unnamed: U$313.P$1, U$318.P$2
unnamed: U$315.P$1, U$318.P$7
unnamed: U$320.P$1, U$324.P$4
unnamed: U$319.P$1, U$324.P$2
unnamed: U$321.P$1, U$324.P$7
unnamed: U$326.P$1, U$330.P$4
unnamed: U$325.P$1, U$330.P$2
unnamed: U$327.P$1, U$330.P$7
unnamed: U$332.P$1, U$336.P$4
unnamed: U$331.P$1, U$336.P$2
unnamed: U$333.P$1, U$336.P$7
unnamed: U$338.P$1, U$342.P$4
unnamed: U$337.P$1, U$342.P$2
unnamed: U$339.P$1, U$342.P$7
unnamed: U$344.P$1, U$348.P$4
unnamed: U$343.P$1, U$348.P$2
unnamed: U$345.P$1, U$348.P$7
unnamed: U$350.P$1, U$354.P$4
unnamed: U$349.P$1, U$354.P$2
unnamed: U$351.P$1, U$354.P$7
unnamed: U$356.P$1, U$360.P$4
unnamed: U$355.P$1, U$360.P$2
unnamed: U$357.P$1, U$360.P$7
unnamed: U$362.P$1, U$366.P$4
unnamed: U$361.P$1, U$366.P$2
unnamed: U$363.P$1, U$366.P$7
unnamed: U$368.P$1, U$372.P$4
unnamed: U$367.P$1, U$372.P$2
unnamed: U$369.P$1, U$372.P$7
unnamed: U$374.P$1, U$378.P$4
unnamed: U$373.P$1, U$378.P$2
unnamed: U$375.P$1, U$378.P$7
unnamed: U$380.P$1, U$384.P$4
unnamed: U$379.P$1, U$384.P$2
unnamed: U$381.P$1, U$384.P$7
unnamed: U$386.P$1, U$390.P$4
unnamed: U$385.P$1, U$390.P$2
unnamed: U$387.P$1, U$390.P$7
unnamed: U$392.P$1, U$396.P$4
unnamed: U$391.P$1, U$396.P$2
unnamed: U$393.P$1, U$396.P$7
unnamed: U$398.P$1, U$402.P$4
unnamed: U$397.P$1, U$402.P$2
unnamed: U$399.P$1, U$402.P$7
unnamed: U$404.P$1, U$408.P$4
unnamed: U$403.P$1, U$408.P$2
unnamed: U$405.P$1, U$408.P$7
unnamed: U$410.P$1, U$414.P$4
unnamed: U$409.P$1, U$414.P$2
unnamed: U$411.P$1, U$414.P$7
unnamed: U$416.P$1, U$420.P$4
unnamed: U$415.P$1, U$420.P$2
unnamed: U$417.P$1, U$420.P$7
unnamed: U$422.P$1, U$426.P$4
unnamed: U$421.P$1, U$426.P$2
unnamed: U$423.P$1, U$426.P$7
unnamed: U$428.P$1, U$432.P$4
unnamed: U$427.P$1, U$432.P$2
unnamed: U$429.P$1, U$432.P$7
unnamed: U$434.P$1, U$438.P$4
unnamed: U$433.P$1, U$438.P$2
unnamed: U$435.P$1, U$438.P$7
unnamed: U$440.P$1, U$444.P$4
unnamed: U$439.P$1, U$444.P$2
unnamed: U$441.P$1, U$444.P$7
unnamed: U$446.P$1, U$450.P$4
unnamed: U$445.P$1, U$450.P$2
unnamed: U$447.P$1, U$450.P$7
unnamed: U$452.P$1, U$456.P$4
unnamed: U$451.P$1, U$456.P$2
unnamed: U$453.P$1, U$456.P$7
unnamed: U$458.P$1, U$462.P$4
unnamed: U$457.P$1, U$462.P$2
unnamed: U$459.P$1, U$462.P$7
unnamed: U$464.P$1, U$468.P$4
unnamed: U$463.P$1, U$468.P$2
unnamed: U$465.P$1, U$468.P$7
unnamed: U$470.P$1, U$474.P$4
unnamed: U$469.P$1, U$474.P$2
unnamed: U$471.P$1, U$474.P$7
unnamed: U$476.P$1, U$480.P$4
unnamed: U$475.P$1, U$480.P$2
unnamed: U$477.P$1, U$480.P$7
unnamed: U$482.P$1, U$486.P$4
unnamed: U$481.P$1, U$486.P$2
unnamed: U$483.P$1, U$486.P$7
unnamed: U$488.P$1, U$492.P$4
unnamed: U$487.P$1, U$492.P$2
unnamed: U$489.P$1, U$492.P$7
unnamed: U$494.P$1, U$498.P$4
unnamed: U$493.P$1, U$498.P$2
unnamed: U$495.P$1, U$498.P$7
unnamed: U$500.P$1, U$504.P$4
unnamed: U$499.P$1, U$504.P$2
unnamed: U$501.P$1, U$504.P$7
unnamed: U$506.P$1, U$510.P$4
unnamed: U$505.P$1, U$510.P$2
unnamed: U$507.P$1, U$510.P$7
unnamed: U$512.P$1, U$516.P$4
unnamed: U$511.P$1, U$516.P$2
unnamed: U$513.P$1, U$516.P$7
unnamed: U$518.P$1, U$522.P$4
unnamed: U$517.P$1, U$522.P$2
unnamed: U$519.P$1, U$522.P$7
unnamed: U$524.P$1, U$528.P$4
unnamed: U$523.P$1, U$528.P$2
unnamed: U$525.P$1, U$528.P$7
unnamed: U$530.P$1, U$534.P$4
unnamed: U$529.P$1, U$534.P$2
unnamed: U$531.P$1, U$534.P$7
unnamed: U$536.P$1, U$540.P$4
unnamed: U$535.P$1, U$540.P$2
unnamed: U$537.P$1, U$540.P$7
unnamed: U$542.P$1, U$546.P$4
unnamed: U$541.P$1, U$546.P$2
unnamed: U$543.P$1, U$546.P$7
unnamed: U$548.P$1, U$552.P$4
unnamed: U$547.P$1, U$552.P$2
unnamed: U$549.P$1, U$552.P$7
unnamed: U$554.P$1, U$558.P$4
unnamed: U$553.P$1, U$558.P$2
unnamed: U$555.P$1, U$558.P$7
unnamed: U$560.P$1, U$564.P$4
unnamed: U$559.P$1, U$564.P$2
unnamed: U$561.P$1, U$564.P$7
unnamed: U$566.P$1, U$570.P$4
unnamed: U$565.P$1, U$570.P$2
unnamed: U$567.P$1, U$570.P$7
unnamed: U$572.P$1, U$576.P$4
unnamed: U$571.P$1, U$576.P$2
unnamed: U$573.P$1, U$576.P$7
unnamed: U$578.P$1, U$582.P$4
unnamed: U$577.P$1, U$582.P$2
unnamed: U$579.P$1, U$582.P$7
unnamed: U$584.P$1, U$588.P$4
unnamed: U$583.P$1, U$588.P$2
unnamed: U$585.P$1, U$588.P$7
unnamed: U$590.P$1, U$594.P$4
unnamed: U$589.P$1, U$594.P$2
unnamed: U$591.P$1, U$594.P$7
unnamed: U$596.P$1, U$600.P$4
unnamed: U$595.P$1, U$600.P$2
unnamed: U$597.P$1, U$600.P$7
unnamed: U$602.P$1, U$606.P$4
unnamed: U$601.P$1, U$606.P$2
unnamed: U$603.P$1, U$606.P$7
unnamed: U$608.P$1, U$612.P$4
unnamed: U$607.P$1, U$612.P$2
unnamed: U$609.P$1, U$612.P$7
unnamed: U$614.P$1, U$618.P$4
unnamed: U$613.P$1, U$618.P$2
unnamed: U$615.P$1, U$618.P$7
unnamed: U$620.P$1, U$624.P$4
unnamed: U$619.P$1, U$624.P$2
unnamed: U$621.P$1, U$624.P$7
unnamed: U$626.P$1, U$630.P$4
unnamed: U$625.P$1, U$630.P$2
unnamed: U$627.P$1, U$630.P$7
unnamed: U$632.P$1, U$636.P$4
unnamed: U$631.P$1, U$636.P$2
unnamed: U$633.P$1, U$636.P$7
unnamed: U$638.P$1, U$642.P$4
unnamed: U$637.P$1, U$642.P$2
unnamed: U$639.P$1, U$642.P$7
unnamed: U$644.P$1, U$648.P$4
unnamed: U$643.P$1, U$648.P$2
unnamed: U$645.P$1, U$648.P$7
